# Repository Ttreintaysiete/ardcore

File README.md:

# Eurorack Ardcore 2017
This is the repository for the tuned sketches, schematics and board files of the new 2017 version 20Objects Ardcore. The Ardcore is an Arduino based module created by Darwin Grosse as his final work for MS. You can find more information on the orignal project in his website http://20objects.com/ardcore/.

So far there are a couple of versions of the ardcore, the original one by 20Objects which was a PCB only, AFAIK it was intended for dotcom and 5U formats and all the wiring with the panel has to be done manually. This version has 4 AnalogInputs, 2 of them are potentiometers and the other 2 are inputs. It also has 2 digital outputs (i.e. for triggers).

The [original sketches](https://github.com/darwingrosse/ArdCore-Code/commits/master) were first published by Darwin back in 2012. This project originally was a DIY PCB only project.

Later on SnazzyFX published an eurorack format of the module and (as Dan a.k.a. told me) it was long out of stock due its success for a couple of years. 

There are plenty of threads in muffwiggler talking about different DIY versions, back in 2013 we made our own version for bananas.

The Ardcore is not so well known module but its a power house due its flexibility, it has several sketches that are very usefull and fun to play, but more important the Ardcore is a module that tries to embed the Arduino philosophy into the modular synthesizer community which is to allow musicians, artists and engineers to easly create microcontroller based modules.

Due its digital nature, the ardcore is very good for creating CV sources that are otherwise more complex to create with hardware (like a drunken walk), but it also can create audio with the DAC.

# Our implementation of Ardcore

So we decided to make a skiff friendly, DIY Ardcore with several improvements:

* double the number of __analog inputs__. So now each AnalogInput has a potentiometer that is normalized to 5v when nothing is connected, when you plug something into the corresponding jack you can still use the potentiometer to attenuate the incommin signal. All analog inputs are protected with diodes (1n4148) so voltage will be cliped to the microcontroller range always (0v-5v). In any case you can use the pot as mentioned to attenuate the incomming signal.

* double the number of __digital outputs__. The original ardcore had 2 digital outputs, in this version we put D2 and D3 for a total of 4. This outputs are driven by the Tristate buffer widely used in digital modules like Mutable Instruments, so you can both isolate microcontroller pin from the outside world at the same time to upscale the voltage and buffer it. So if you plug an output signal into the digital outputs you can't damage the micro controller.

* double the number of __digital inputs__, the original and snazzy Ardcore had 1 multipurpouse digital input labeled as "clock". This input is connected to a pin in the micro controler with support for interrupts which are very usefull when you want to have "responsive" or non blocking behaviours on your sketch. In the new ardcore we added a second digital input labeled __RESET__ which is also connected to another interrupt pin. All the existing sketches were created for the previous hardware versions of the ardcore so they __don't__ use this pin.

* Upgraded DAC, from parallel to SPI and from 8bit to 12bit. This upgrade was both a must go mainly because of the size of the IC and that its easy to source it, also the PCB has less trace (since parallel communication uses 8 connections from atmega328 to the DAC, in comparison with the SPI that only uses 3 wires.

* 8hp Skiff friendly.

# The bad things

Some of the decissions taken during the pcb design have downsides.

* This version of the Ardcore is __non-banana friendly__ :( ... we are very sorry for this because we have many modules in bananas and love them, but it was a design decision to make it work with the disconnections on the minijacks. This is by far (in our opinion) the biggest downside.

* When upgrading the DAC from parallel to SPI we lose all the "bit" traces from the parallel connections, so its not possible to easly create an expander for this version of the module.

* Another problem from upgrading the DAC is that the original sketches that used it, need a small tweak on the code in order to work properlly. This is based on the Euroardcore but with the mcp4921

  * you need to add to the beggining of any sketch using the DAC,
    ```
    #include <SPI.h>
    #include <DAC_MCP49xx.h>
    DAC_MCP49xx dac(DAC_MCP49xx::MCP4921, 10);
    ```
  * also you need to add the following code at the end of the __setup()__ so the DAC is properlly initialized:
    ```
    dac.setBuffer(true);        //  Set FALSE for 5V vref.
    dac.setGain(1);             //  "1" for 5V vref. "2" for 2.5V vref.
    dac.setPortWrite(true); 
    ```
  * and finally replace the __dacOutput()__ and __dacOutputfast()__ to be something like:
    ```
     void dacOutput(long v)
    {
      dac.outputA(v);
    }
    ```

* No USB, need a programer.. the original Ardcore had either an arduino nano or a ftdi IC with USB on the board, so you can directly upload your sketches. With this version you need an external programmer that uses ISP, we recommend the official [AVRISP mkii](http://www.atmel.com/tools/avrispmkii.aspx).

# License:

This software and hardware is licensed under the Creative Commons __Attribution-NonCommercial__ license. This license allows you to tweak and build upon the code for non-commercial purposes, without the requirement to license derivative works on the same terms. If you wish to use this (or derived) work for commercial work or usage of the PCBS, please contact 20 Objects LLC its website (www.20objects.com).

For more information on the Creative Commons CC BY-NC license, visit http://creativecommons.org/licenses/

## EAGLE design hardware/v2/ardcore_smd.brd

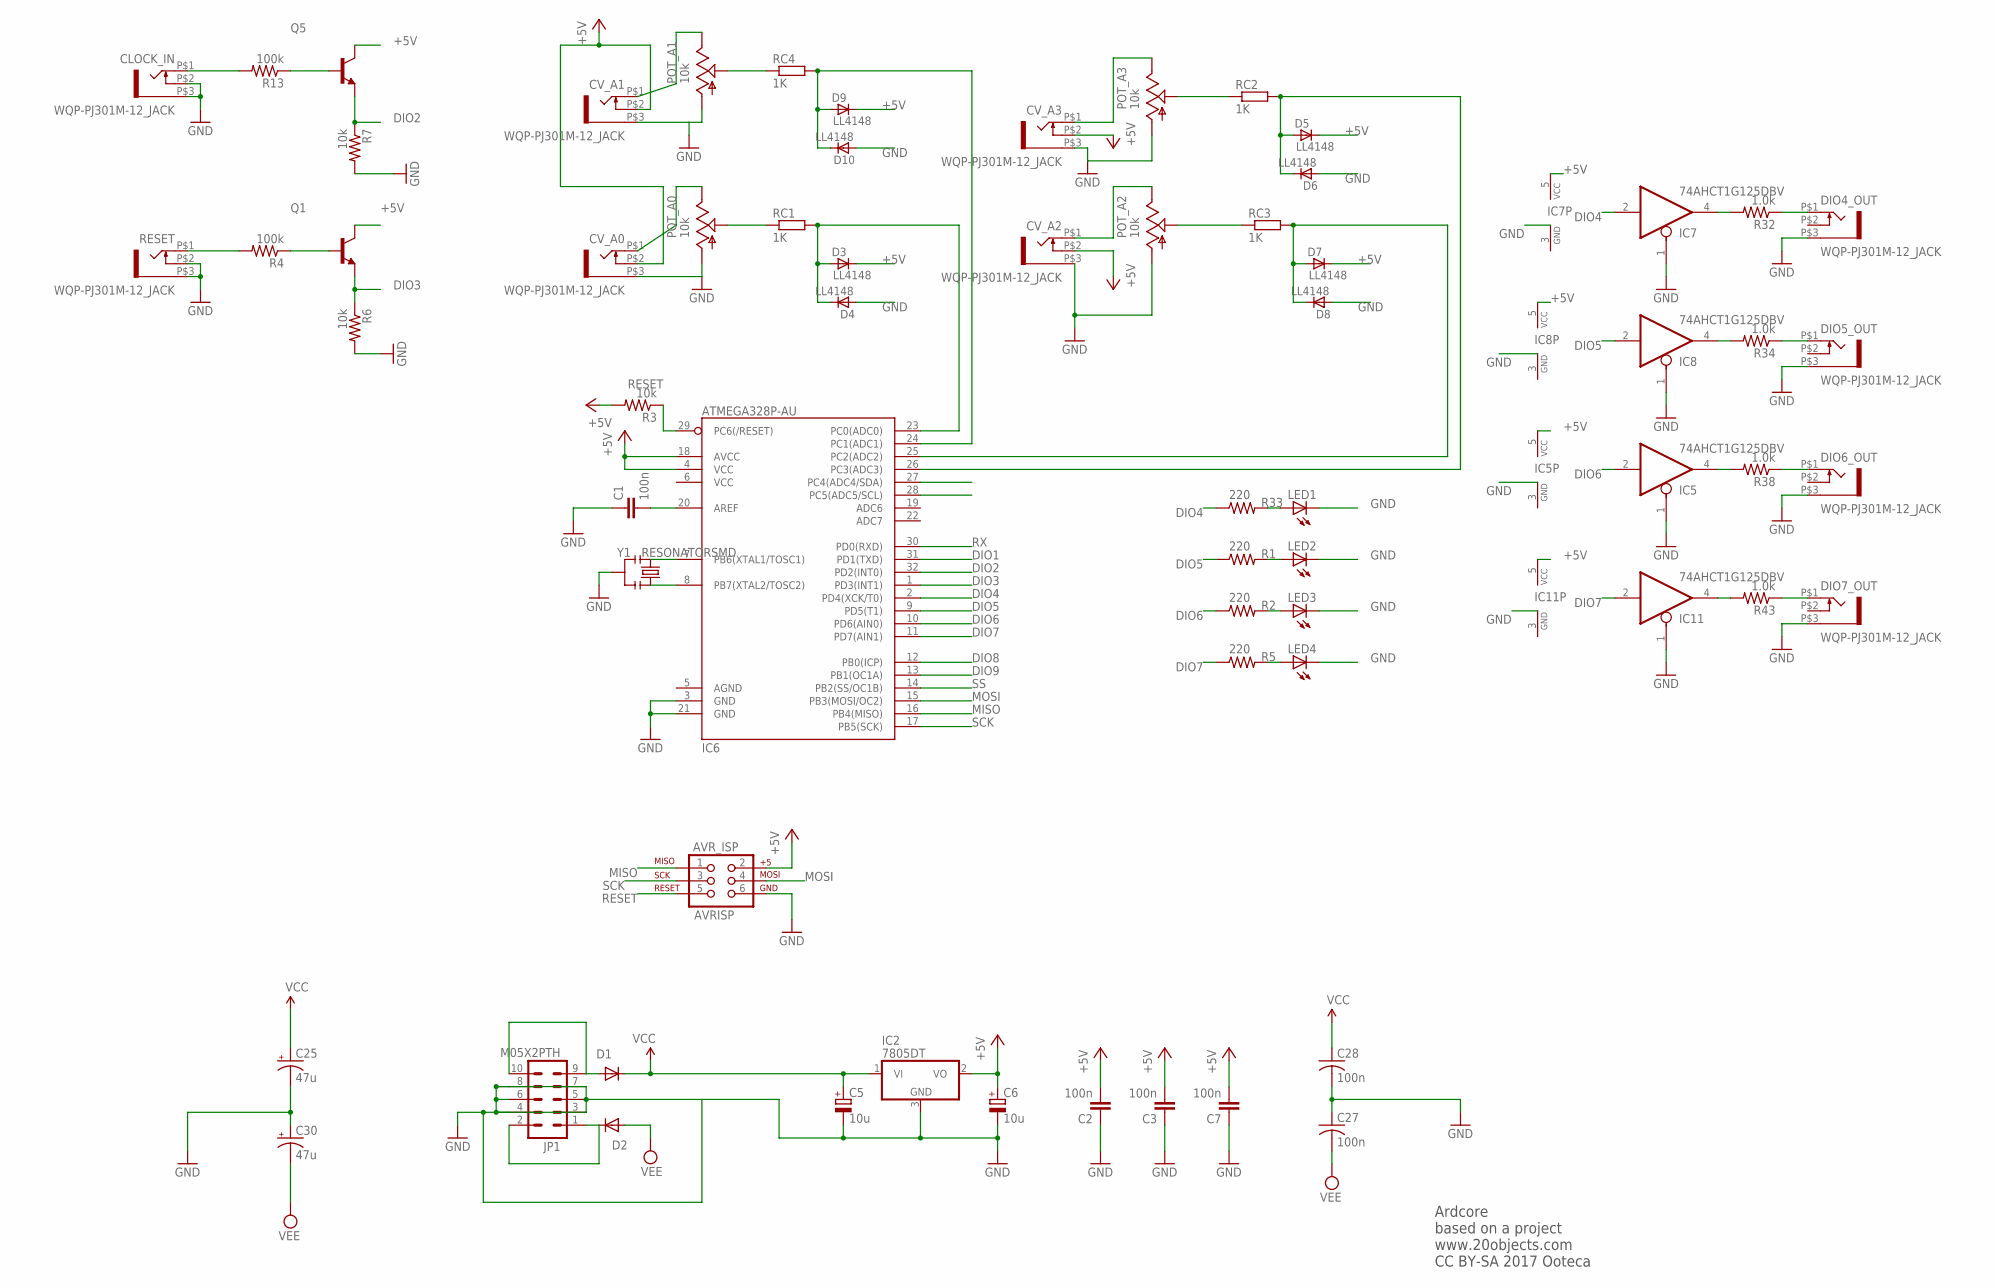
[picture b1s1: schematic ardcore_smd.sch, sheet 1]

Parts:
AVR_ISP: AVRISP; 2X3
C1, C2, C3, C27, C28: 100n; C0603
C5, C6: 10u; E2,5-5
C7: 100n; C0805
C25, C30: 47u; PANASONIC_D
CLOCK_IN: WQP-PJ301M-12_JACK
CV_A0, CV_A1, CV_A2, CV_A3: WQP-PJ301M-12_JACK
D1, D2: 1N5819; SOD123
D3, D4, D5, D6, D7, D8, D9, D10: LL4148; SOD80_DO213AA_MINIMELF
DIO4_OUT, DIO5_OUT, DIO6_OUT, DIO7_OUT: WQP-PJ301M-12_JACK
IC2: 7805DT; TO252
IC5, IC7, IC8, IC11: 74AHCT1G125DBV; SOT23-5
IC6: ATMEGA328P-AU; TQFP32-08
JP1: M05X2PTH; AVR_ICSP
LED1, LED2, LED3, LED4: LED3MM
POT_A0, POT_A1, POT_A2, POT_A3: 10k; ALPS_POT_VERTICAL
Q1, Q5: MMBT3904LT1-NPN-SOT23-BEC; SOT23-BEC
R1, R2, R5, R33: 220; R0603
R3, R6, R7: 10k; R0603
R4, R13: 100k; R0603
R32, R34, R38, R43: 1.0k; R0603
RC1, RC2, RC3, RC4: 1K; R0603
RESET: WQP-PJ301M-12_JACK
Y1: RESONATORSMD; RESONATOR-SMD

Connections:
+5V: AVR_ISP.2, C2.2, C3.2, C6.+, C7.2, CV_A0.P$2 (3), CV_A1.P$2 (3), CV_A2.P$2 (3), CV_A3.P$2 (3), D3.C, D5.C, D7.C, D9.C, IC2.2 (VO), IC5.5 (VCC), IC6.4 (VCC), IC6.18 (AVCC), IC7.5 (VCC), IC8.5 (VCC), IC11.5 (VCC), Q1.C, Q5.C, R3.2; also elsewhere on the board
ANI1: D9.A, D10.C, IC6.24 (PC1(ADC1)), RC4.2
ANI2: D3.A, D4.C, IC6.23 (PC0(ADC0)), RC1.2
ANI3: D5.A, D6.C, IC6.26 (PC3(ADC3)), RC2.2
ANI4: D7.A, D8.C, IC6.25 (PC2(ADC2)), RC3.2
DIO1: IC6.31 (PD1(TXD))
DIO2: IC6.32 (PD2(INT0)), Q5.E, R7.1
DIO3: IC6.1 (PD3(INT1)), Q1.E, R6.1
DIO4: IC6.2 (PD4(XCK/T0)), IC7.2 (I), R33.1
DIO5: IC6.9 (PD5(T1)), IC8.2 (I), R1.1
DIO6: IC5.2 (I), IC6.10 (PD6(AIN0)), R2.1
DIO7: IC6.11 (PD7(AIN1)), IC11.2 (I), R5.1
DIO8: IC6.12 (PB0(ICP))
DIO9: IC6.13 (PB1(OC1A))
GND: AVR_ISP.6, C1.1, C2.1, C3.1, C5.-, C6.-, C7.1, C25.-, C27.1, C28.2, C30.+, CLOCK_IN.P$2 (3), CLOCK_IN.P$3 (1), CV_A0.P$3 (1), CV_A1.P$3 (1), CV_A2.P$3 (1), CV_A3.P$3 (1), D4.A, D6.A, D8.A, D10.A, DIO4_OUT.P$3 (1), DIO5_OUT.P$3 (1), DIO6_OUT.P$3 (1), DIO7_OUT.P$3 (1), IC2.3 (GND), IC5.1 (OE), IC5.3 (GND), IC6.3 (GND), IC6.21 (GND), IC7.1 (OE), IC7.3 (GND), IC8.1 (OE), IC8.3 (GND), IC11.1 (OE), IC11.3 (GND), JP1.3, JP1.4, JP1.5, JP1.6, JP1.7, JP1.8, LED1.K (C), LED2.K (C), LED3.K (C), LED4.K (C), POT_A0.P$3 (A), POT_A1.P$3 (A), POT_A2.P$3 (A), POT_A3.P$3 (A), R6.2, R7.2, RESET.P$2 (3), RESET.P$3 (1), Y1.2; also elsewhere on the board
MISO: AVR_ISP.1, IC6.16 (PB4(MISO))
MOSI: AVR_ISP.4, IC6.15 (PB3(MOSI/OC2)); also elsewhere on the board
unnamed: CV_A2.P$1 (2), POT_A2.P$1 (E)
unnamed: D1.A, JP1.9, JP1.10
unnamed: D2.C, JP1.1, JP1.2
unnamed: DIO6_OUT.P$1 (2), R38.1
unnamed: C1.2, IC6.20 (AREF)
unnamed: DIO5_OUT.P$1 (2), R34.1
unnamed: DIO7_OUT.P$1 (2), R43.1
unnamed: DIO4_OUT.P$1 (2), R32.1
unnamed: CV_A3.P$1 (2), POT_A3.P$1 (E)
unnamed: IC7.4 (O), R32.2
unnamed: Q1.B, R4.1
unnamed: R4.2, RESET.P$1 (2)
unnamed: IC8.4 (O), R34.2
unnamed: Q5.B, R13.1
unnamed: IC6.7 (PB6(XTAL1/TOSC1)), Y1.1
unnamed: IC6.8 (PB7(XTAL2/TOSC2)), Y1.3
unnamed: LED2.A, R1.2
unnamed: LED3.A, R2.2
unnamed: CLOCK_IN.P$1 (2), R13.2
unnamed: LED4.A, R5.2
unnamed: CV_A0.P$1 (2), POT_A0.P$1 (E)
unnamed: POT_A3.P$2 (S), RC2.1
unnamed: CV_A1.P$1 (2), POT_A1.P$1 (E)
unnamed: POT_A2.P$2 (S), RC3.1
unnamed: POT_A0.P$2 (S), RC1.1
unnamed: POT_A1.P$2 (S), RC4.1
unnamed: IC5.4 (O), R38.2
unnamed: IC11.4 (O), R43.2
unnamed: LED1.A, R33.2
RESET: AVR_ISP.5, IC6.29 (PC6(/RESET)), R3.1
RX: IC6.30 (PD0(RXD))
SCK: AVR_ISP.3, IC6.17 (PB5(SCK)); also elsewhere on the board
SS: IC6.14 (PB2(SS/OC1B)); also elsewhere on the board
SW_BLUE: IC6.28 (PC5(ADC5/SCL))
SW_YELLOW: IC6.27 (PC4(ADC4/SDA))
VCC: C5.+, C25.+, C28.1, D1.C, IC2.1 (VI); also elsewhere on the board
VEE: C27.2, C30.-, D2.A; also elsewhere on the board

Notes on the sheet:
Ardcore based on a project www.20objects.com CC BY-SA 2017 Ooteca

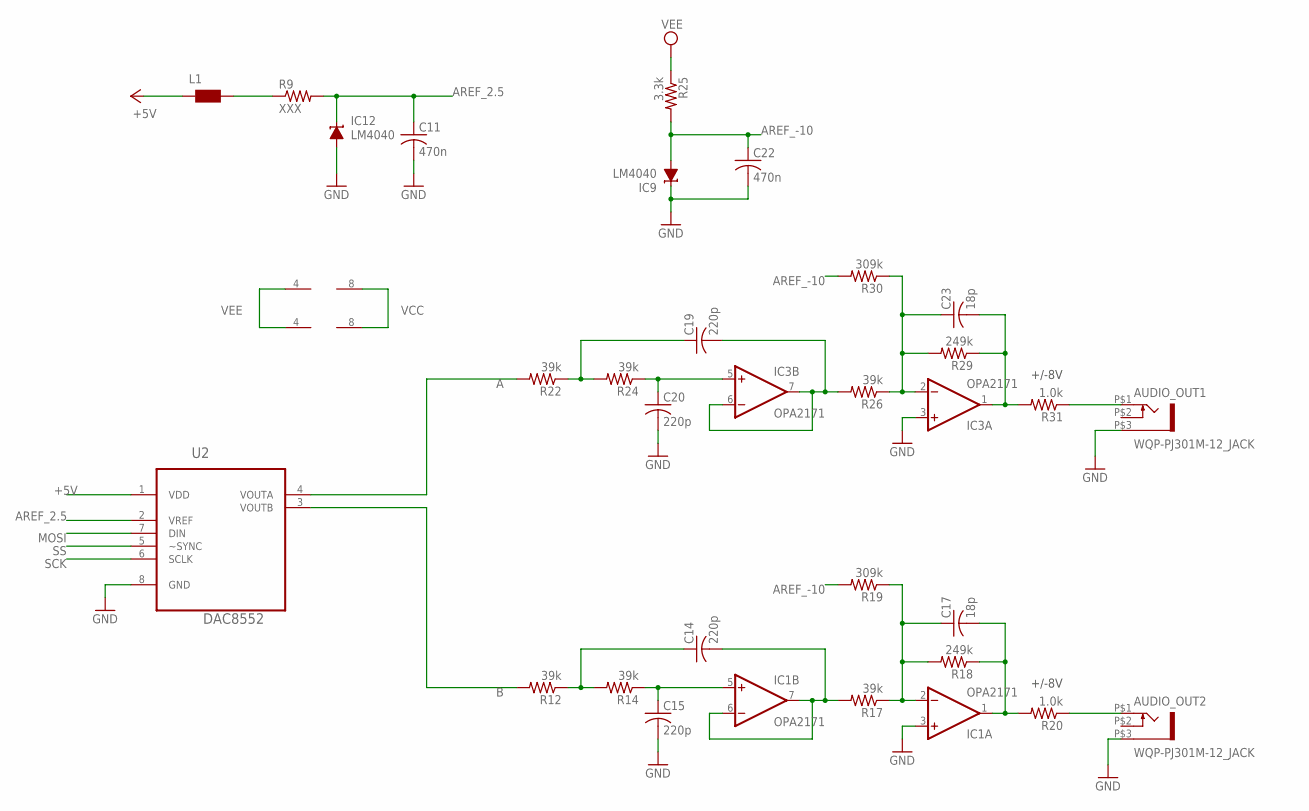
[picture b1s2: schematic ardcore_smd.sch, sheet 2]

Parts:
AUDIO_OUT1, AUDIO_OUT2: WQP-PJ301M-12_JACK
C11, C22: 470n; C0603
C14, C15, C19, C20: 220p; C0603
C17, C23: 18p; C0603
IC1, IC3: OPA2171; SO08
IC9, IC12: LM4040; DBZ_R-PDSO-G3
L1: WE-CBF_0603; 0603
R9: XXX; R0603
R12, R14, R17, R22, R24, R26: 39k; R0603
R18, R29: 249k; R0603
R19, R30: 309k; R0603
R20, R31: 1.0k; R0603
R25: 3.3k; R0603
U2: DAC8552; SOP65P490X110-8N

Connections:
+5V: L1.1, U2.1 (VDD); also elsewhere on the board
A: R22.2, U2.4 (VOUTA)
AREF_2.5: C11.1, IC12.1 (C), R9.2, U2.2 (VREF)
AREF_-10: C22.1, IC9.2 (A), R19.2, R25.2, R30.2
B: R12.2, U2.3 (VOUTB)
BI_OUT: C17.2, IC1.1 (OUT), R18.1, R20.2
BI_OUT1: C23.2, IC3.1 (OUT), R29.1, R31.2
F_CV: C17.1, IC1.2 (-IN), R17.1, R18.2, R19.1
F_CV1: C23.1, IC3.2 (-IN), R26.1, R29.2, R30.1
GND: AUDIO_OUT1.P$3 (1), AUDIO_OUT2.P$3 (1), C11.2, C15.2, C20.2, C22.2, IC1.3 (+IN), IC3.3 (+IN), IC9.1 (C), IC12.2 (A), U2.8 (GND); also elsewhere on the board
MOSI: U2.7 (DIN); also elsewhere on the board
unnamed: C14.1, R12.1, R14.2
unnamed: AUDIO_OUT2.P$1 (2), R20.1
unnamed: C19.2, IC3.6 (-IN), IC3.7 (OUT), R26.2
unnamed: C20.1, IC3.5 (+IN), R24.1
unnamed: C19.1, R22.1, R24.2
unnamed: AUDIO_OUT1.P$1 (2), R31.1
unnamed: L1.2, R9.1
unnamed: C14.2, IC1.6 (-IN), IC1.7 (OUT), R17.2
unnamed: C15.1, IC1.5 (+IN), R14.1
SCK: U2.6 (SCLK); also elsewhere on the board
SS: U2.5 (~SYNC); also elsewhere on the board
VCC: IC1.8 (V+), IC3.8 (V+); also elsewhere on the board
VEE: IC1.4 (V-), IC3.4 (V-), R25.1; also elsewhere on the board

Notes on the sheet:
+/-8V

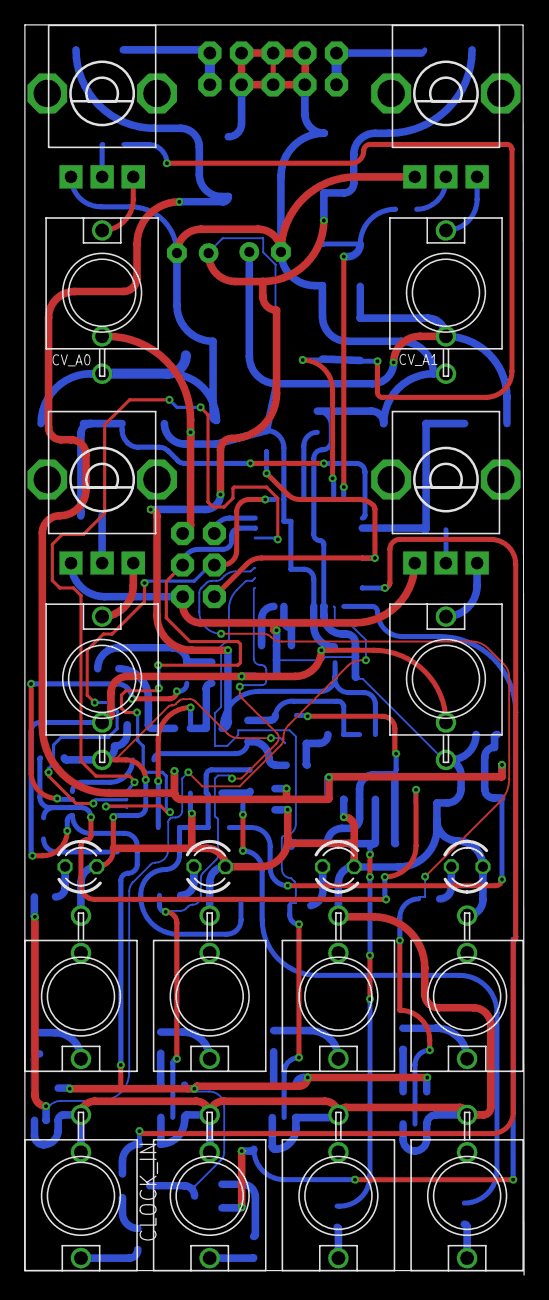
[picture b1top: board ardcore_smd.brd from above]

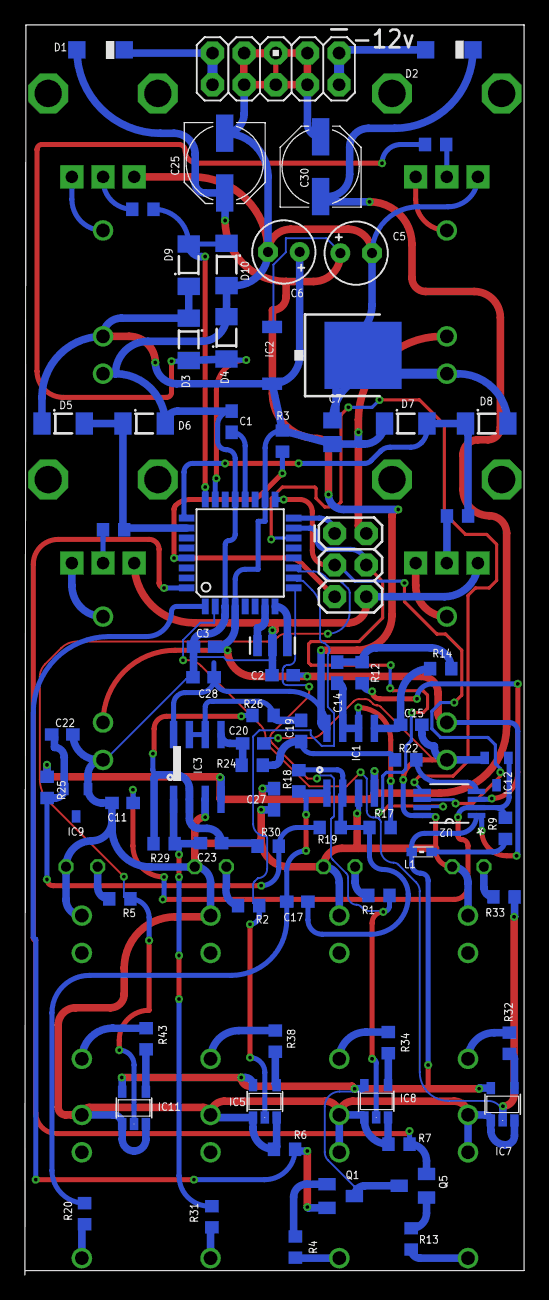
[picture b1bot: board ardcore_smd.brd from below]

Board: 2 copper layers, 40.1 x 100.4 mm, 96 parts (76 on the bottom side), 65 nets.

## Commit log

2017-09-27 Adding sketches
2017-09-27 Initial commit with all sketches
2017-09-27 Changes on supermario facdrums
2017-09-27 Adding clockdivider to fac drums
2017-09-27 Renaming test
2017-09-27 Cleaning sm sketch
2017-09-28 Adding voltage controlled clockdivider to fac drums sketch
2017-09-29 Adding images
2017-09-29 Adding descriptions
    adding images
2017-09-29 More text for the README
2017-09-29 Adding new ardcore image
2017-09-29 Adding more info about nu-ardcore
2017-10-02 Adding building guide and bom
2017-10-02 Adding fixes to BOM
2017-10-02 Adding fix for bom
2017-10-02 Adding building Image
2017-10-02 Adding some fixes to building doc
2017-10-02 Adding some...
2017-10-02 Adding schematics, boards and Gerbers
2017-10-02 Adding non-banana disclaimer
2017-10-02 And disclaimer
2017-10-02 moving files into software
2017-10-02 fixes in doc
2017-10-02 doc fixes
2017-10-04 minor changes
2017-10-26 adding mouser project
    for the lazy like... every single human been.
2017-11-09 Update BUILDING.md
    fix 100p for 100n cap
2017-11-09 Update BUILDING.md
    adding 47u caps
2017-11-20 Changing R50 to 47k to have better gain on output, this was corrected on the Schematics, Board, BOM list and Mouser Project link, also fix in the __dac.setGain(1);__ instruction of the DAC, to use 5v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
2017-11-20 Changing exported bom CSV
2017-11-20 Adding MCP4921 librar instructions to the repo
2017-11-23 Adding alternative suggested building docs
2018-01-12 Update BUILDING.md
    Added note to connect power during programming of fuses or sketches
2018-01-15 Updating building doc so R50 is now 47k
2018-02-06 Adding fix for facdrums
2018-02-18 Adding Snazzy FM with DAC changes
2018-02-26 Adding libs and binaries
2018-02-26 Changing path to image
2018-02-26 Adding lib
2018-04-01 Adding version 2 files
2018-04-02 New components
2018-04-06 removing 3v3 reg
2018-04-07 almost routed
2018-04-16 Adding some
2018-05-02 Adding version
2018-05-02 changes on panel
2019-01-04 Adding v2 fixed gerbers
2019-01-11 updating gerbers
